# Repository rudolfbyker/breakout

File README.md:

# breakout
Various breakout PCBs for prototyping

## Useful code

- https://github.com/KiCad/kicad-python
- https://github.com/KiCad/kicad-library-utils

## Useful info

- [Microchop Packaging Specification](https://www.microchip.com/quality/packaging-specifications)

## Mixed license

- All copyrights of datasheets, application notes, and similar documents belong to their respective owners. They are only included in this repository for convenience.
- PCB design files, Gerber files, scripts, etc. are under GNU GPLv3. See `LICENSE`.

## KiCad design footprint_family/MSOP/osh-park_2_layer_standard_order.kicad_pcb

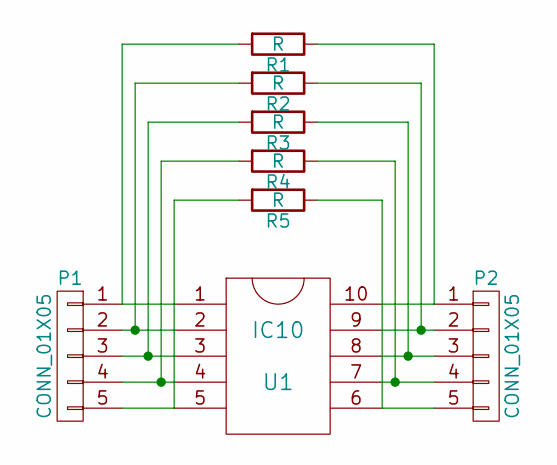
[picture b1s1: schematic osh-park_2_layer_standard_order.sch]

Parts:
P1: CONN_01X05; pin-1x05-sq
P2: CONN_01X05; pin-1x05
R1, R2, R3, R4, R5: R; R_0805_HandSoldering
U1: IC10; MSOP-10

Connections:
unnamed: P1.1, R1.2, U1.1
unnamed: P1.2, R2.2, U1.2
unnamed: P1.3, R3.2, U1.3
unnamed: P1.4, R4.2, U1.4
unnamed: P1.5, R5.2, U1.5
unnamed: P2.1, R1.1, U1.10
unnamed: P2.2, R2.1, U1.9
unnamed: P2.3, R3.1, U1.8
unnamed: P2.4, R4.1, U1.7
unnamed: P2.5, R5.1, U1.6

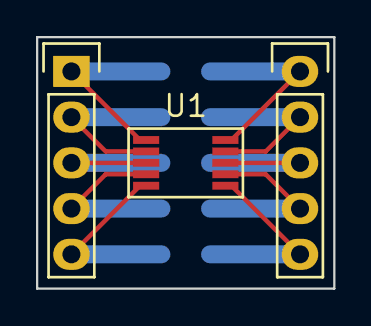
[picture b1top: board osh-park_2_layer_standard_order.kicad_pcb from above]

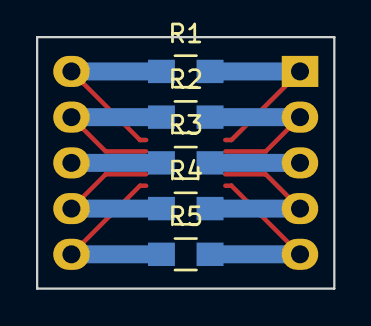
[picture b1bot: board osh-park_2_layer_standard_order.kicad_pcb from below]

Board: 2 copper layers, 16.5 x 14.0 mm, 8 parts (5 on the bottom side), 10 nets.

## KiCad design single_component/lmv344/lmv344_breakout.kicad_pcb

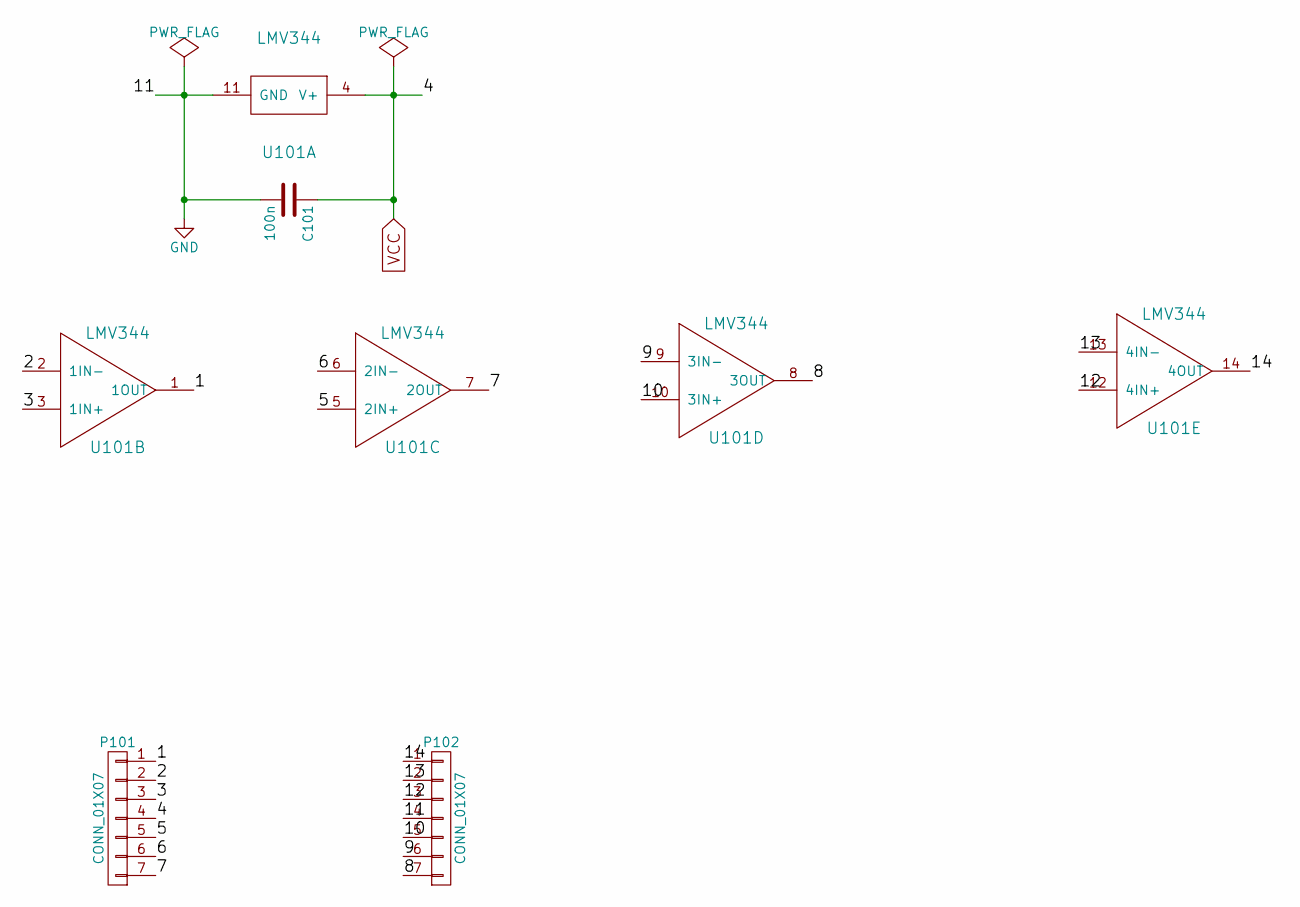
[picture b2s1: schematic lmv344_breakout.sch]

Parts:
C101: 100n; C_0805_HandSoldering
P101, P102: CONN_01X07; Pin_Header_Straight_1x07
U101: LMV344; TSSOP-14_4.4x5mm_Pitch0.65mm-0.25mm_clearance

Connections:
/1: P101.1, U101.1 (1OUT)
/2: P101.2, U101.2 (1IN-)
/3: P101.3, U101.3 (1IN+)
/5: P101.5, U101.5 (2IN+)
/6: P101.6, U101.6 (2IN-)
/7: P101.7, U101.7 (2OUT)
/8: P102.7, U101.8 (3OUT)
/9: P102.6, U101.9 (3IN-)
/10: P102.5, U101.10 (3IN+)
/12: P102.3, U101.12 (4IN+)
/13: P102.2, U101.13 (4IN-)
/14: P102.1, U101.14 (4OUT)
GND: C101.2, P102.4, U101.11 (GND)
VCC: C101.1, P101.4, U101.4 (V+)

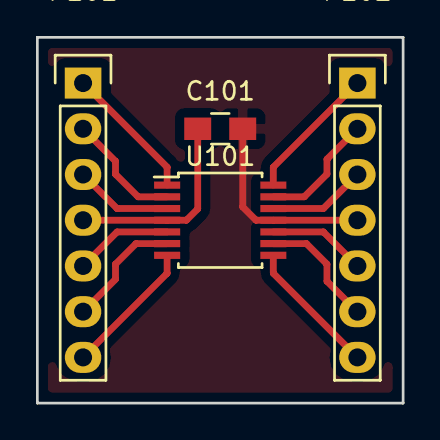
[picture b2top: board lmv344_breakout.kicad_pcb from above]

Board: 2 copper layers, 20.3 x 20.3 mm, 4 parts (0 on the bottom side), 14 nets.

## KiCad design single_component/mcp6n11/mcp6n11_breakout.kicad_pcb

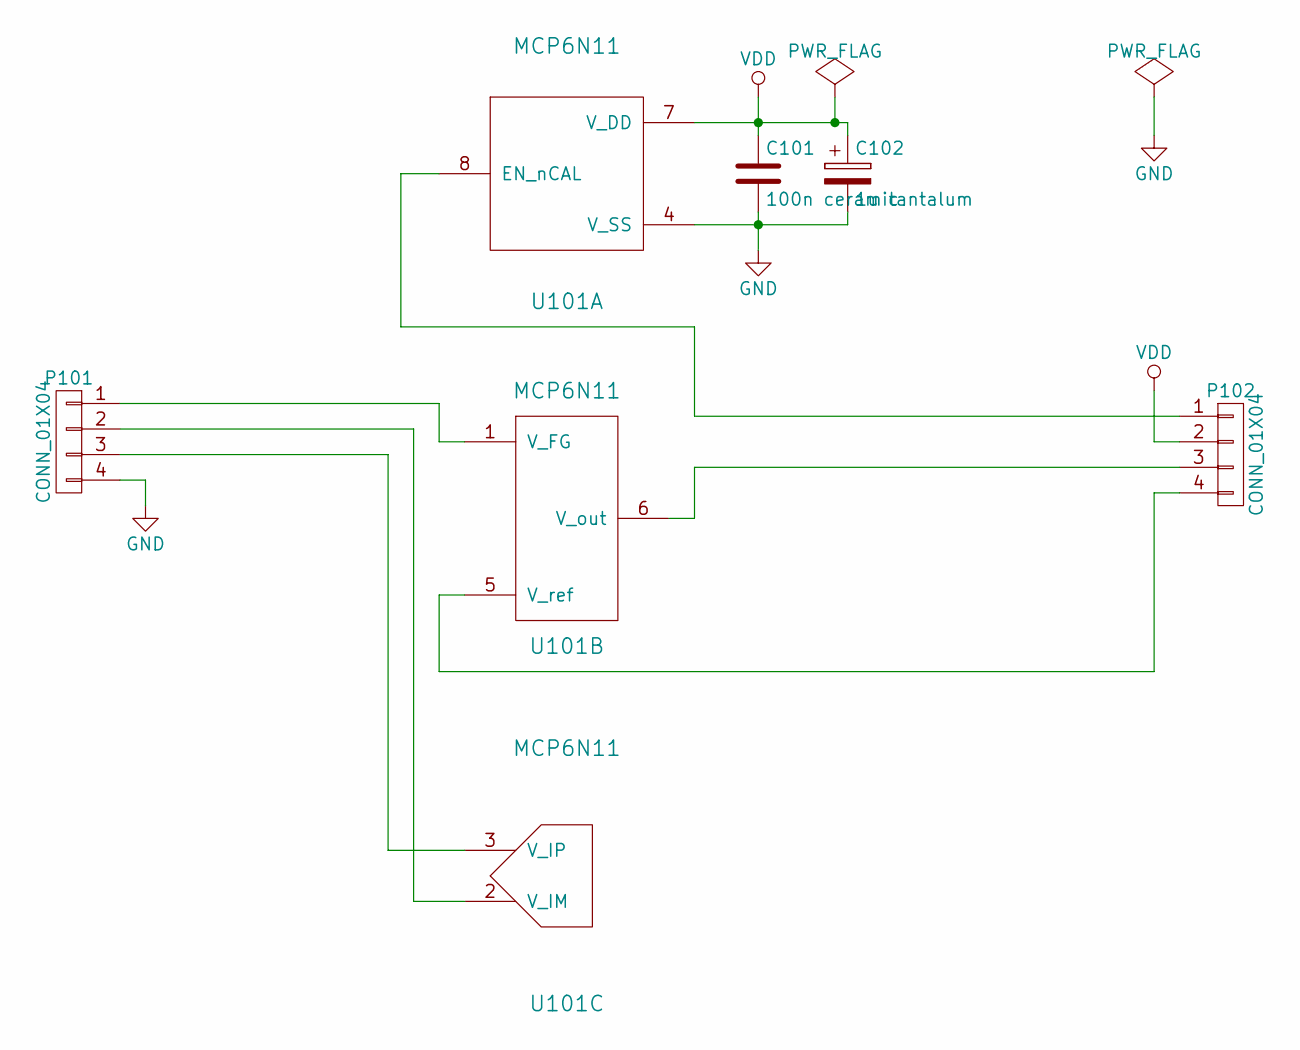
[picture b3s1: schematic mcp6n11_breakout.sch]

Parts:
C101: 100n ceramic; C_0805_HandSoldering
C102: 1u tantalum; TantalC_SizeB_EIA-3528_HandSoldering
P101, P102: CONN_01X04; Pin_Header_Straight_1x04
U101: MCP6N11; SOIC-8_3.9x4.9mm_Pitch1.27mm

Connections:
GND: C101.2, C102.2, P101.4, U101.4 (V_SS)
unnamed: P101.1, U101.1 (V_FG)
unnamed: P101.2, U101.2 (V_IM)
unnamed: P101.3, U101.3 (V_IP)
unnamed: P102.1, U101.8 (EN_nCAL)
unnamed: P102.3, U101.6 (V_out)
unnamed: P102.4, U101.5 (V_ref)
VDD: C101.1, C102.1, P102.2, U101.7 (V_DD)

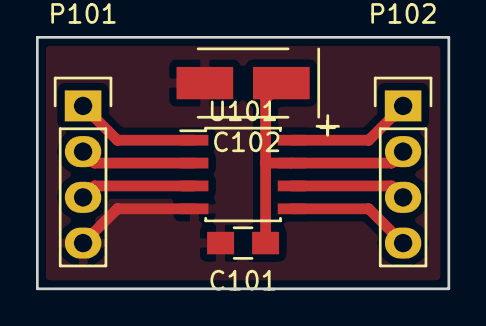
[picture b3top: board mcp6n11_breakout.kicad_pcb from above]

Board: 2 copper layers, 22.9 x 14.0 mm, 5 parts (0 on the bottom side), 8 nets.

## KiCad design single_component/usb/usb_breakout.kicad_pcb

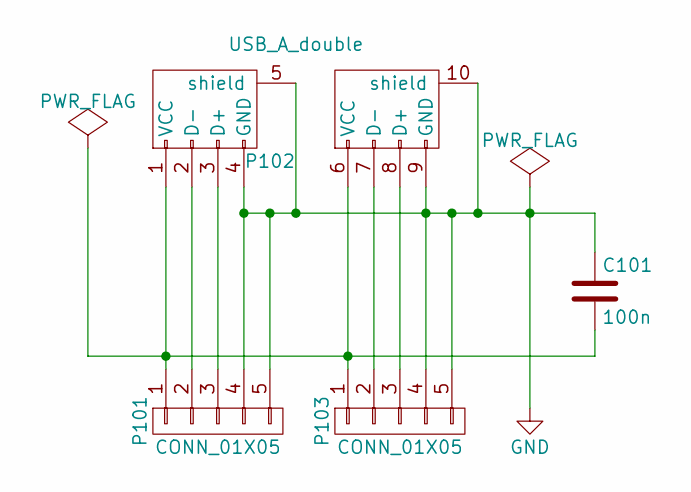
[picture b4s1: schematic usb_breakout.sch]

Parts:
C101: 100n; C_0805_HandSoldering
P101, P103: CONN_01X05; Pin_Header_Straight_1x05
P102: USB_A_double

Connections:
GND: C101.1, P101.4, P101.5, P102.4 (GND), P102.5 (shield), P102.9 (GND), P102.10 (shield), P103.4, P103.5
unnamed: C101.2, P101.1, P102.1 (VCC), P102.6 (VCC), P103.1
unnamed: P101.2, P102.2 (D-)
unnamed: P101.3, P102.3 (D+)
unnamed: P102.7 (D-), P103.2
unnamed: P102.8 (D+), P103.3

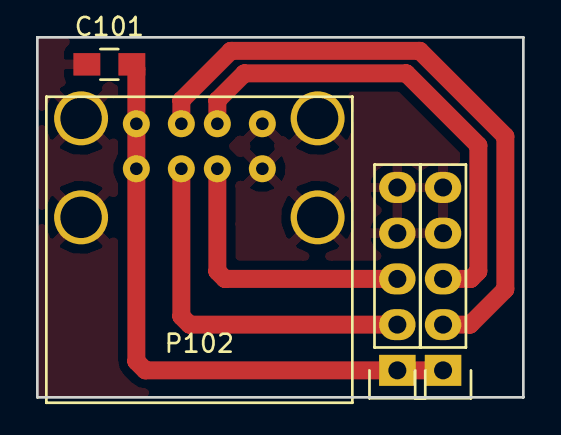
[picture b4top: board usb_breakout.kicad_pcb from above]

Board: 2 copper layers, 27.0 x 20.0 mm, 4 parts (0 on the bottom side), 6 nets.

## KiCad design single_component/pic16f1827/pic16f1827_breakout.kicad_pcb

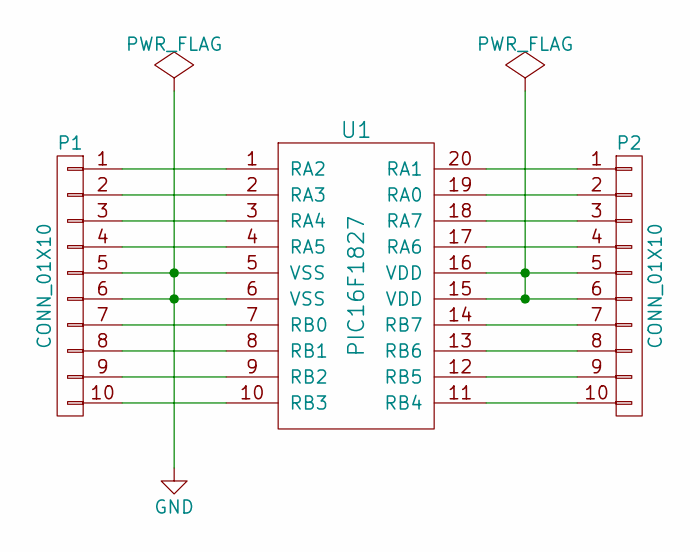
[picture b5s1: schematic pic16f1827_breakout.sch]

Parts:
P1, P2: CONN_01X10; Pin_Header_Straight_1x10
U1: PIC16F1827; SSOP-20

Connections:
GND: P1.5, P1.6, U1.5 (VSS), U1.6 (VSS)
unnamed: P1.1, U1.1 (RA2)
unnamed: P1.2, U1.2 (RA3)
unnamed: P1.3, U1.3 (RA4)
unnamed: P1.4, U1.4 (RA5)
unnamed: P1.7, U1.7 (RB0)
unnamed: P1.8, U1.8 (RB1)
unnamed: P1.9, U1.9 (RB2)
unnamed: P1.10, U1.10 (RB3)
unnamed: P2.1, U1.20 (RA1)
unnamed: P2.2, U1.19 (RA0)
unnamed: P2.3, U1.18 (RA7)
unnamed: P2.4, U1.17 (RA6)
unnamed: P2.5, P2.6, U1.15 (VDD), U1.16 (VDD)
unnamed: P2.7, U1.14 (RB7)
unnamed: P2.8, U1.13 (RB6)
unnamed: P2.9, U1.12 (RB5)
unnamed: P2.10, U1.11 (RB4)

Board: 2 copper layers, 3 parts (0 on the bottom side), 18 nets, no tracks yet.

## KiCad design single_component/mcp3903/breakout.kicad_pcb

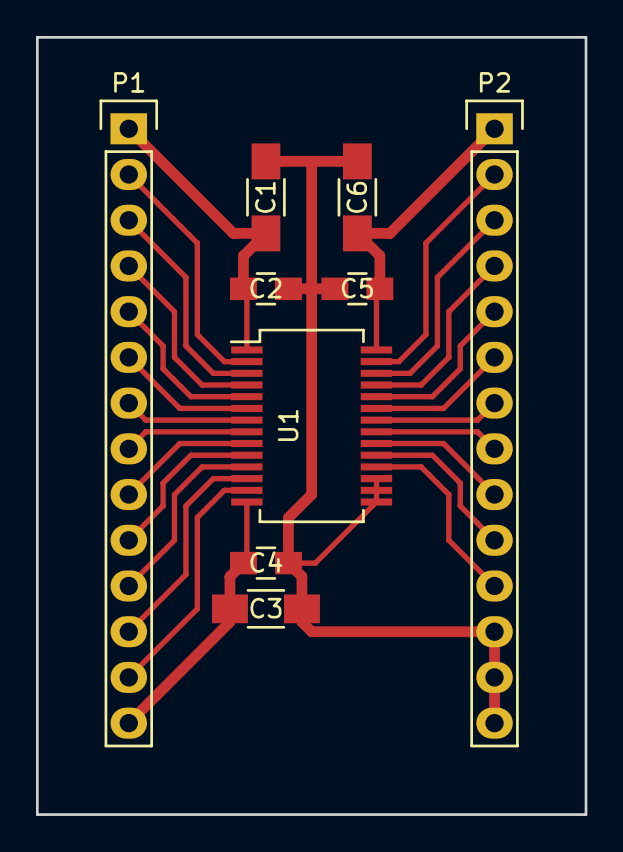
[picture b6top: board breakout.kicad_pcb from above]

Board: 2 copper layers, 30.5 x 43.2 mm, 9 parts (0 on the bottom side), 26 nets.

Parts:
C1, C3, C6: 10u; C_1206_HandSoldering
C2, C4, C5: 100n; C_0805_HandSoldering
P1, P2: CONN_01X14; Pin_Header_Straight_1x14
U1: M10u3903-I/SS; SSOP-28_5.3x10.2mm_Pitch0.65mm_Clearance0.25mm

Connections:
GND: C1.2, C2.2, C3.2, C4.2, C5.2, C6.2, P2.12, P2.13, P2.14, U1.15, U1.16, U1.17
unnamed: C1.1, C2.1, P1.1, U1.1
unnamed: C3.1, C4.1, P1.14, U1.14
unnamed: C5.1, C6.1, P2.1, U1.28
unnamed: P1.2, U1.2
unnamed: P1.3, U1.3
unnamed: P1.4, U1.4
unnamed: P1.5, U1.5
unnamed: P1.6, U1.6
unnamed: P1.7, U1.7
unnamed: P1.8, U1.8
unnamed: P1.9, U1.9
unnamed: P1.10, U1.10
unnamed: P1.11, U1.11
unnamed: P1.12, U1.12
unnamed: P1.13, U1.13
unnamed: P2.2, U1.27
unnamed: P2.3, U1.26
unnamed: P2.4, U1.25
unnamed: P2.5, U1.24
unnamed: P2.6, U1.23
unnamed: P2.7, U1.22
unnamed: P2.8, U1.21
unnamed: P2.9, U1.20
unnamed: P2.10, U1.19
unnamed: P2.11, U1.18

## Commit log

2016-12-09 Added various breakout board designs which I had laying around
2016-12-09 Ignore .bak files and .idea project files.
2016-12-09 Added 10-pin component
2016-12-09 Added MSOP project from osh park template
2016-12-09 Generate pin footprints with 1mm drill holes from the standard KiCAD footprints using a script
2016-12-09 Update names, descriptions and silkscreen value
2016-12-09 Removed manually created pins
2016-12-09 Two output modules for each input module: One with square copper at pin 1, and one with only oval shapes.
2016-12-09 Schematic and layout for MSOP chips.
2016-12-09 Smaller PCB for MSOP
2016-12-09 Hide values and references using a script
2016-12-09 Ignore .pyc files
